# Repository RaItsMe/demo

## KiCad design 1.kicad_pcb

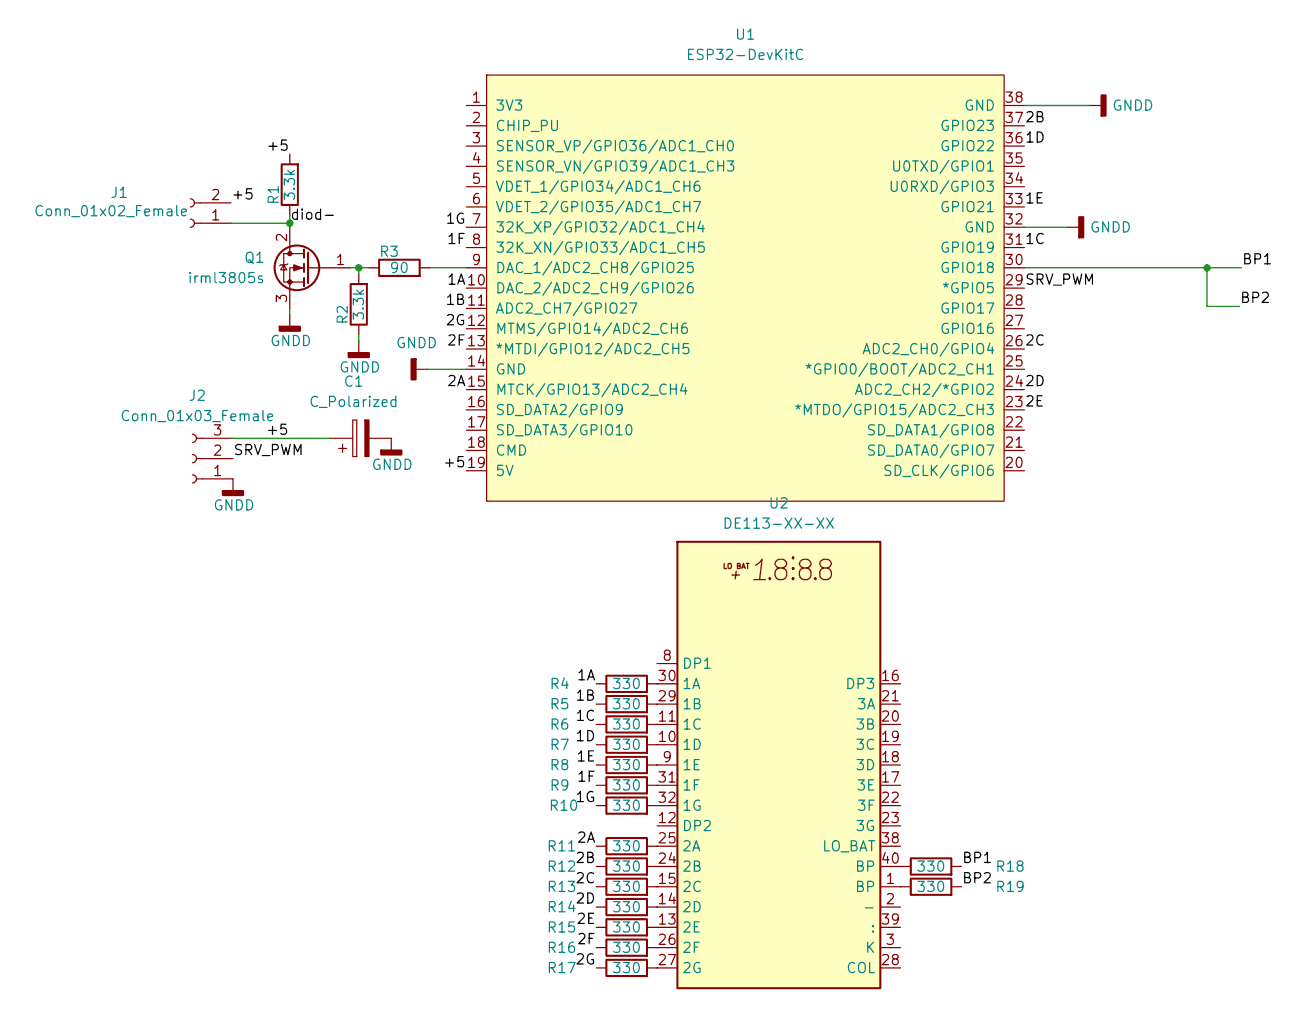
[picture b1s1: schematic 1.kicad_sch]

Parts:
C1: C_Polarized; CP_Radial_D10.0mm_P5.00mm
J1: Conn_01x02_Female; PinHeader_1x02_P2.54mm_Vertical
J2: Conn_01x03_Female; PinHeader_1x03_P2.54mm_Vertical
Q1: irml3805s; TO-263-2
R1, R2: 3.3k; R_0805_2012Metric_Pad1.20x1.40mm_HandSolder
R3: 90; R_0805_2012Metric_Pad1.20x1.40mm_HandSolder
R4, R5, R6, R7, R8, R9, R10, R11, R12, R13, R14, R15, R16, R17, R18, R19: 330; R_0805_2012Metric_Pad1.20x1.40mm_HandSolder
U1: ESP32-DevKitC
U2: DE113-XX-XX

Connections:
/1A: R4.1, U1.10 (DAC_2/ADC2_CH9/GPIO26)
/1B: R5.1, U1.11 (ADC2_CH7/GPIO27)
/1C: R6.1, U1.31 (GPIO19)
/1D: R7.1, U1.36 (GPIO22)
/1E: R8.1, U1.33 (GPIO21)
/1F: R9.1, U1.8 (32K_XN/GPIO33/ADC1_CH5)
/1G: R10.1, U1.7 (32K_XP/GPIO32/ADC1_CH4)
/2A: R11.1, U1.15 (MTCK/GPIO13/ADC2_CH4)
/2B: R12.1, U1.37 (GPIO23)
/2C: R13.1, U1.26 (ADC2_CH0/GPIO4)
/2D: R14.1, U1.24 (ADC2_CH2/*GPIO2)
/2E: R15.1, U1.23 (*MTDO/GPIO15/ADC2_CH3)
/2F: R16.1, U1.13 (*MTDI/GPIO12/ADC2_CH5)
/2G: R17.1, U1.12 (MTMS/GPIO14/ADC2_CH6)
/+5: C1.1, J1.2, J2.3, R1.2, U1.19 (5V)
/BP1: R18.2, R19.2, U1.30 (GPIO18)
/SRV_PWM: J2.2, U1.29 (*GPIO5)
/diod-: J1.1, Q1.2 (D), R1.1
GNDD: C1.2, J2.1, Q1.3 (S), R2.1, U1.14 (GND), U1.32 (GND), U1.38 (GND)
unnamed: Q1.1 (G), R2.2, R3.1
unnamed: R3.2, U1.9 (DAC_1/ADC2_CH8/GPIO25)
unnamed: R4.2, U2.30 (1A)
unnamed: R5.2, U2.29 (1B)
unnamed: R6.2, U2.11 (1C)
unnamed: R7.2, U2.10 (1D)
unnamed: R8.2, U2.9 (1E)
unnamed: R9.2, U2.31 (1F)
unnamed: R10.2, U2.32 (1G)
unnamed: R11.2, U2.25 (2A)
unnamed: R12.2, U2.24 (2B)
unnamed: R13.2, U2.15 (2C)
unnamed: R14.2, U2.14 (2D)
unnamed: R15.2, U2.13 (2E)
unnamed: R16.2, U2.26 (2F)
unnamed: R17.2, U2.27 (2G)
unnamed: R18.1, U2.40 (BP)
unnamed: R19.1, U2.1 (BP)

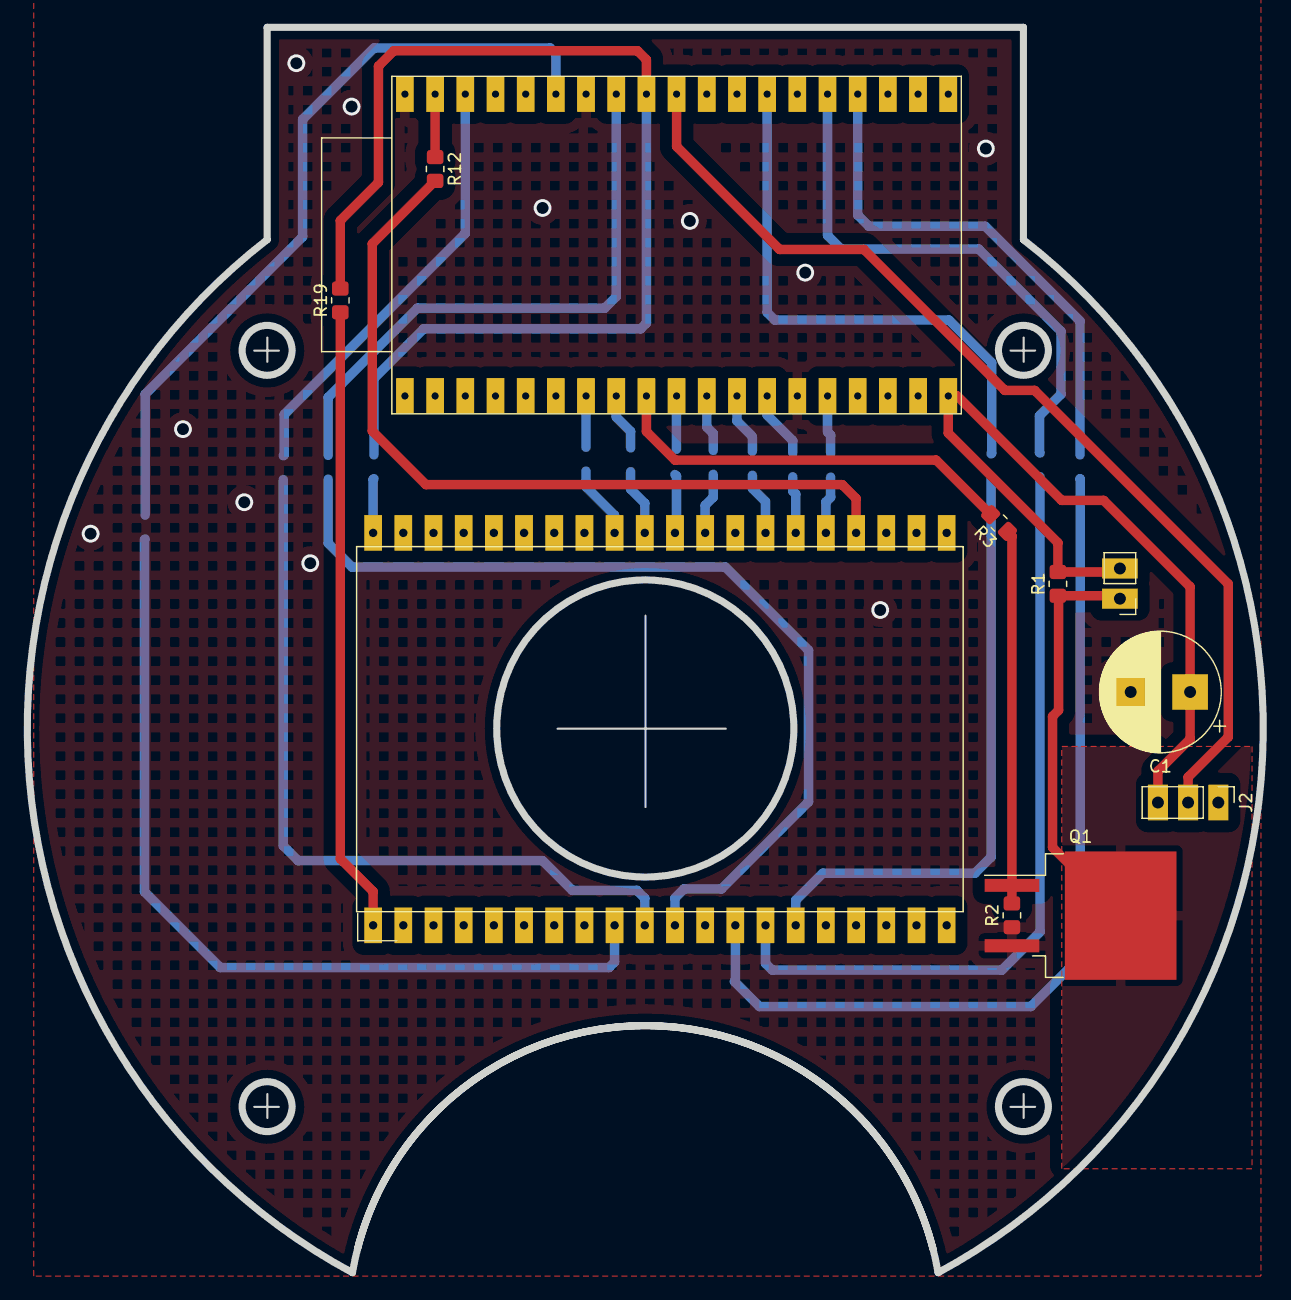
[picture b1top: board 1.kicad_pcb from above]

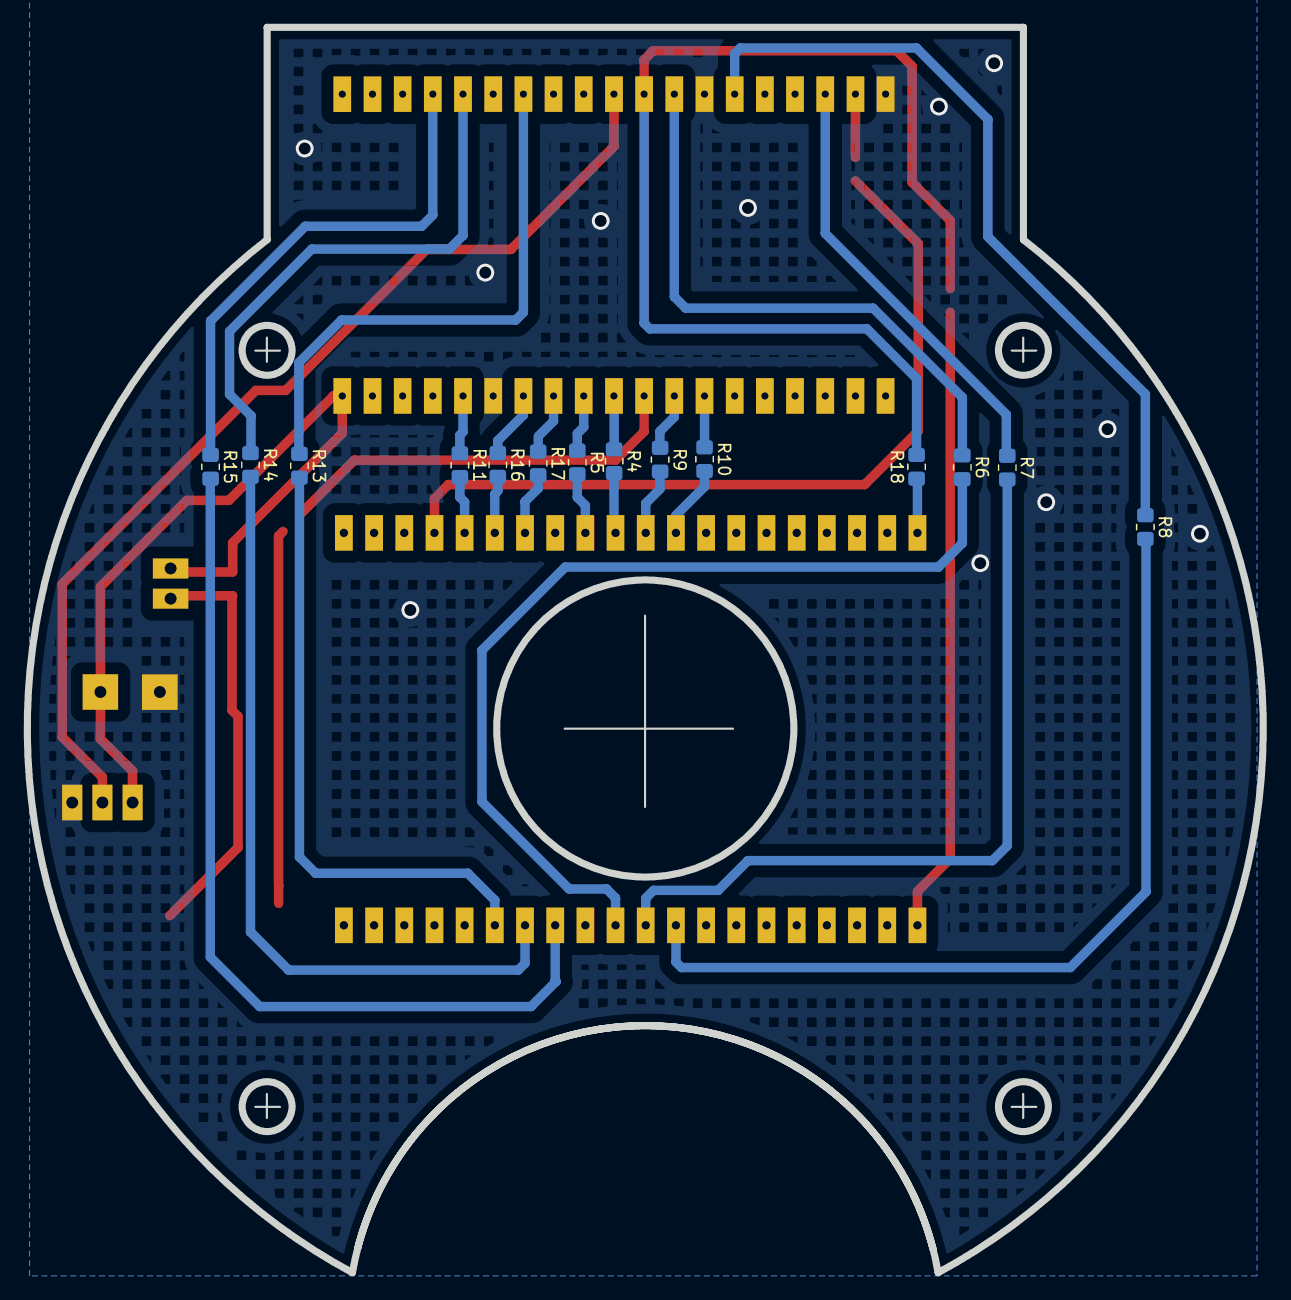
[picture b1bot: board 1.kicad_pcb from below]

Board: 2 copper layers, 104.0 x 104.8 mm, 25 parts (14 on the bottom side), 37 nets.

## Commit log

2022-06-29 init
